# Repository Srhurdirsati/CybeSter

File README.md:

# CyberSter

Cyberster is a portable MP3 player using different electronic modules. It can play music from an SD card and send audio through AUX or Bluetooth. A screen is used to show the menu and song information. The device also uses a Type-C port for power and transferring music files.

## Complete Hardware & BOM Table

Go to bom.csv for BOM 

## Features 

> MP3 playback from SD card

> Scrollable music list

> Basic UI on TFT screen

> Play / Pause / Next / Previous controls

> Volume adjustment

> Sleep mode

> Automatic next-track playback

> Aux Output

The display needs to be just vertically mounted on the mounting poles .

## Usage 

> Install Arduino IDE.

> Install the ESP32 board package.

> Install the required libraries:

> Adafruit VS1053

> Adafruit GFX

> Adafruit ST7789

> SPI

> SD

> Open the firmware file.

> Select your ESP32 board.

> Upload the code.

Now you are done setting it up the firmware . 

Next you will need to plug the battery to the jst connector below the board and make sure its properly connected at appropriate poles. The buttons would be pressed by the 3d model of button which would be inserted from below the top plate at it's desired holes and it will automatically fit in that . No need to solder anything .

## Future Possible Updates

> Bt support

> Inbuilt Speaker

> Playlist

> Better Animations, etc.

## Images

## JLCPCB

This was my most difficult and complex project till now and most timetaking so I just wan't to say that PCB won't feel easy at all if you are a beginner and also make sure u have enough knowledge to start .

TFT = 13 USD, ESP-32 = 7 USD, JLC = 67 

Total = 87 USD With Shipping

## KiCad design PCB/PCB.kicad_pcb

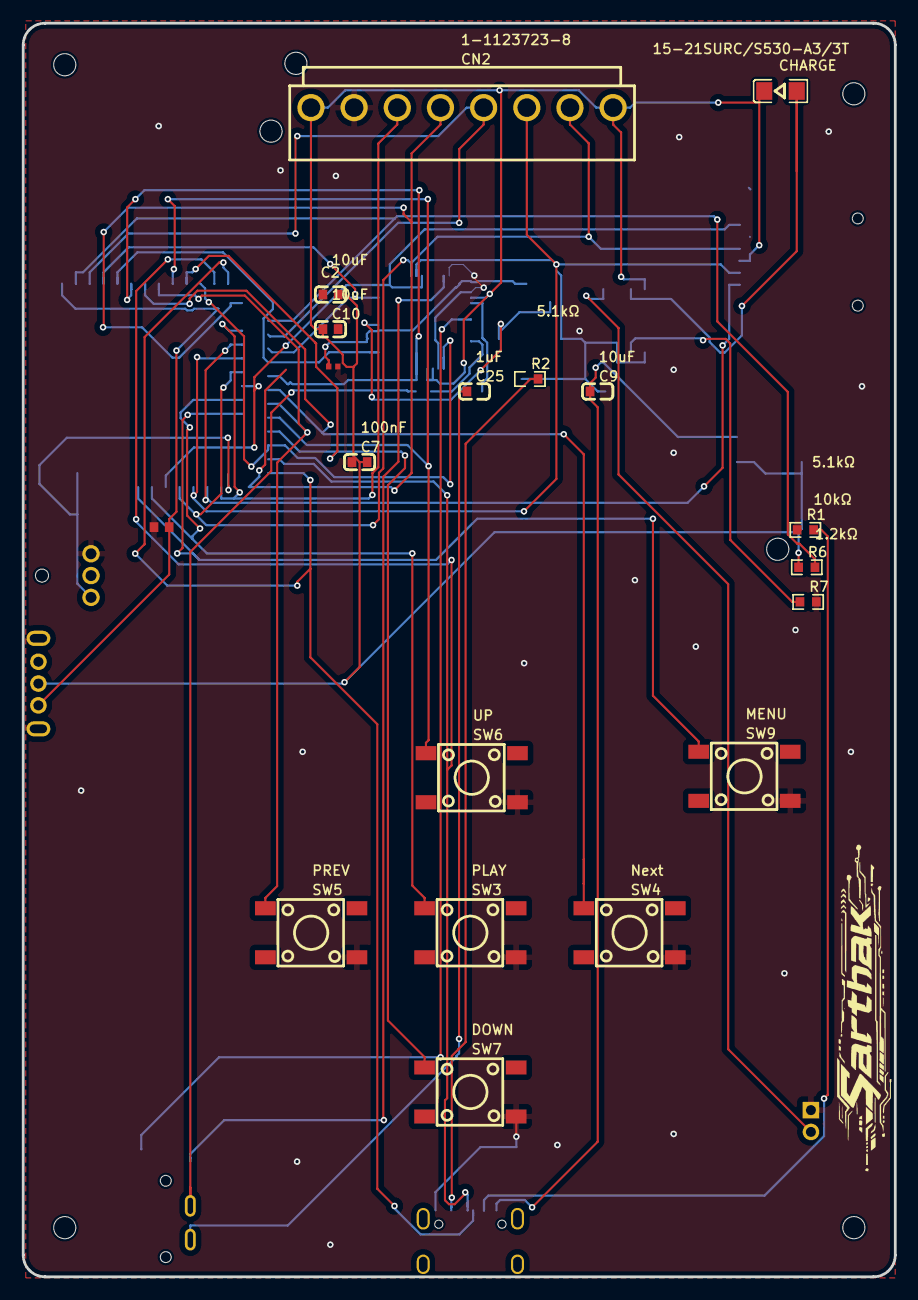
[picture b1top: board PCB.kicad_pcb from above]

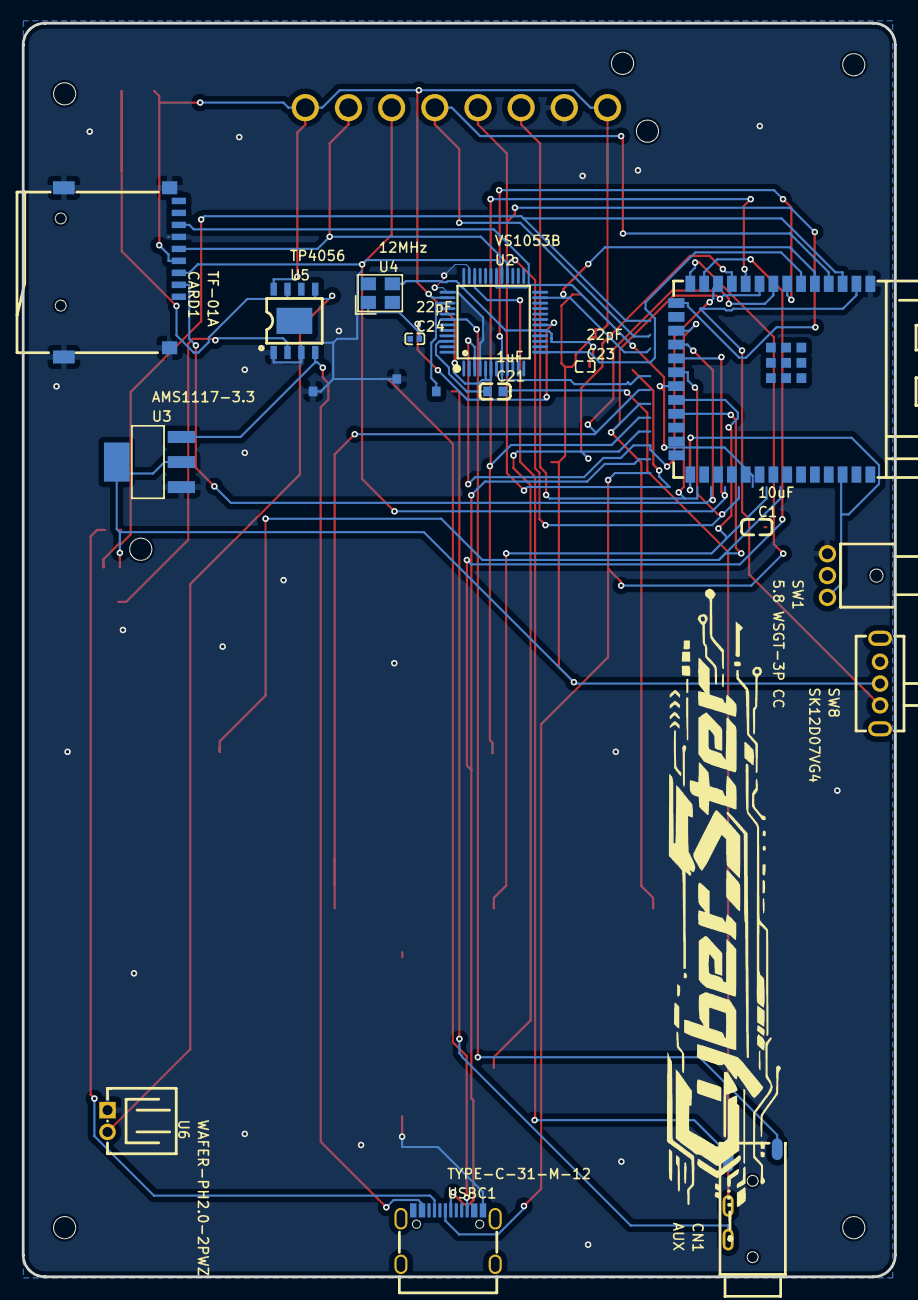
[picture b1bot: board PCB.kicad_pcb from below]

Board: 2 copper layers, 80.0 x 115.0 mm, 39 parts (15 on the bottom side), 38 nets.

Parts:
C1, C2, C9, C10: 10uF; C0603
C7: 100nF; C0603
C21, C25: 1uF; C0603
C23, C24: 22pF; C0402
CARD1: TF-01A; TF-SMD_TF-01A
CHARGE: 15-21SURC/S530-A3/3T; LED1206-R-RD_RED
CN1: AUX; AUDIO-SMD_HC-PJ-320A
CN2: 1-1123723-8; CONN-TH_1-1123723-8
Hole_gge20538: Hole_gge20538
Hole_gge20553: Hole_gge20553
Hole_gge20568: Hole_gge20568
Hole_gge20583: Hole_gge20583
Hole_gge20613: Hole_gge20613
Hole_gge20670: Hole_gge20670
Hole_gge20700: Hole_gge20700
R1, R2: 5.1kΩ; R0603
R6: 10kΩ; R0603
R7: 1.2kΩ; R0603
SW1: 5.8 WSGT-3P CC; SW-TH_3P-L5.8_WSGT-3P-CC
SW3: PLAY; KEY-SMD_4P-L6.0-W6.0-P4.50-LS9.0
SW4: Next; KEY-SMD_4P-L6.0-W6.0-P4.50-LS9.0
SW5: PREV; KEY-SMD_4P-L6.0-W6.0-P4.50-LS9.0
SW6: UP; KEY-SMD_4P-L6.0-W6.0-P4.50-LS9.0
SW7: DOWN; KEY-SMD_4P-L6.0-W6.0-P4.50-LS9.0
SW8: SK12D07VG4; SW-TH_SK12D07VG4
SW9: MENU; KEY-SMD_4P-L6.0-W6.0-P4.50-LS9.0
U1: ESP32; WIRELM-SMD_ESP32-S3-WROOM-1
U2: VS1053B; LQFP-48_L7.0-W7.0-P0.50-LS9.0-BL
U3: AMS1117-3.3; SOT-223-3_L6.5-W3.4-P2.30-LS7.0-BR
U4: 12MHz; CRYSTAL-SMD_4P-L3.2-W2.5-BL
U5: TP4056; ESOP-8_L4.9-W3.9-P1.27-LS6.0-BL-EP
U6: WAFER-PH2.0-2PWZ; CONN-TH_2P-P2.00_GP01-2001WR-2P
USBC1: TYPE-C-31-M-12; USB-C_SMD-TYPE-C-31-M-12_1

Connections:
3V: C2.2, C7.2, C10.1, CARD1.4, CHARGE.2, CN2.1, CN2.8, R6.1, SW8.2, U2.5, U2.6, U2.38, U3.2, U3.4, U5.8
5V: C9.1, U3.3, U5.4, USBC1.A4B9
DETECT: CN1.4, U2.34
GBUF: CN1.1, U2.42
GND: C1.2, C2.1, C7.1, C9.2, C10.2, C23.1, C24.1, CARD1.6, CARD1.10, CARD1.11, CARD1.12, CARD1.13, CN2.2, R1.1, R2.1, R7.2, SW1.3, SW3.4, SW4.4, SW5.4, SW6.4, SW7.4, SW9.4, U1.1, U2.4, U2.35, U2.37, U3.1, U5.1, U5.3, U6.1, USBC1.B1A12
LEFT: C21.2, CN1.3
MENU: SW9.1, U1.23
MISO: CARD1.7, U1.21, U2.30
MOSI: CARD1.3, CN2.6, U1.19, U2.29
NEXT: SW4.1, U1.8
PLAY: SW3.1, U1.22
PREV: SW5.1, U1.9
RIGHT: C25.1, CN1.2
SCLK: CARD1.5, CN2.7, U1.20, U2.28
SDCARDCS: CARD1.2, U1.18
SW3.3: C1.1, SW8.1, U1.2
TFTAO: CN2.5, U1.4
TFTT_RST: CN2.4, U1.15
TFT_CS: CN2.3, U1.17
U1_3: R6.2, U1.3
U1_27: SW1.1, U1.27
U2_39: C25.2, U2.39
U2_46: C21.1, U2.46
U5_2: R7.1, U5.2
U5_5: U5.5, U6.2
U5_7: CHARGE.1, U5.7
USBC1_A5: R1.2, USBC1.A5
USBC1_B5: R2.2, USBC1.B5
USBD+: U1.14, USBC1.A6
USBD-: U1.13, USBC1.A7
V+: SW6.1, U1.10
V-: SW7.1, U1.11
VS1053_DREQ: U1.7, U2.8
VS1053_RST: U1.12, U2.3
VS1053_XCS: U1.5, U2.23
VS1053_XDCS: U1.6, U2.13
XTALI: C24.2, U2.18, U4.1
XTALO: C23.2, U2.17, U4.3

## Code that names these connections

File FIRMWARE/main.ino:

#include <SPI.h>
#include <SD.h>
#include <Adafruit_VS1053.h>
#include <Adafruit_GFX.h>
#include <Adafruit_ST7789.h>

// VS1053
#define VS1053_CS 5
#define VS1053_DCS 6
#define VS1053_DREQ 7
#define VS1053_RST 8

// SD
#define SD_CS 10

// TFT
#define TFT_CS 9
#define TFT_DC 4
#define TFT_RST 3

// Buttons
#define BTN_PLAY 14
#define BTN_NEXT 15
#define BTN_PREV 16
#define BTN_UP 17
#define BTN_DOWN 18
#define BTN_MENU 21

// Battery
#define BAT_ADC 1

#define MAX_SONGS 200
#define SCREEN_W 240
#define SCREEN_H 240

Adafruit_ST7789 tft = Adafruit_ST7789(TFT_CS, TFT_DC, TFT_RST);

Adafruit_VS1053_FilePlayer player =
Adafruit_VS1053_FilePlayer(
VS1053_RST,
VS1053_CS,
VS1053_DCS,
VS1053_DREQ,
SD_CS
);

String songList[MAX_SONGS];
int songCount = 0;

int selected = 0;
int currentSong = -1;

bool playing = false;

int volume = 20;

int scrollOffset = 0;

unsigned long lastUI = 0;

void scanFiles(File dir) {

while(true){

File entry = dir.openNextFile();

if(!entry) break;

String name = entry.name();

if(name.endsWith(".MP3") || name.endsWith(".mp3")){

songList[songCount++] = name;

}

entry.close();

}

}

float readBattery(){

int raw = analogRead(BAT_ADC);

float voltage = raw * (3.3 / 4095.0) * 2;

return voltage;

}

int batteryPercent(){

float v = readBattery();

if(v >= 4.2) return 100;
if(v >= 4.0) return 85;
if(v >= 3.8) return 60;
if(v >= 3.6) return 40;
if(v >= 3.4) return 20;
return 5;

}

void drawHeader(){

tft.fillRect(0,0,240,30,ST77XX_BLUE);

tft.setCursor(5,8);
tft.setTextColor(ST77XX_WHITE);
tft.setTextSize(2);
tft.print("MP3 Player");

int bat = batteryPercent();

tft.setCursor(180,8);
tft.print(bat);
tft.print("%");

}

void drawList(){

tft.fillRect(0,30,240,170,ST77XX_BLACK);

for(int i=0;i<6;i++){

int index = scrollOffset + i;

if(index >= songCount) break;

if(index == selected){

tft.fillRect(0,30 + i*28,240,28,ST77XX_GREEN);

tft.setTextColor(ST77XX_BLACK);

}else{

tft.setTextColor(ST77XX_WHITE);

}

tft.setCursor(10,40 + i*28);

tft.print(songList[index]);

}

}

void drawPlayer(){

tft.fillRect(0,30,240,170,ST77XX_BLACK);

tft.setCursor(10,40);
tft.print("Playing:");

tft.setCursor(10,70);
tft.print(songList[currentSong]);

}

void drawProgress(){

if(!player.playingMusic) return;

uint32_t pos = player.currentPosition();
uint32_t len = player.playingMusicSize;

if(len == 0) return;

int w = (pos * 200) / len;

tft.drawRect(20,200,200,10,ST77XX_WHITE);

tft.fillRect(20,200,w,10,ST77XX_GREEN);

}

void playSelected(){

currentSong = selected;

player.stopPlaying();

player.startPlayingFile(songList[currentSong].c_str());

playing = true;

drawPlayer();

}

void handleButtons(){

if(!digitalRead(BTN_UP)){

selected--;

if(selected < 0) selected = 0;

if(selected < scrollOffset) scrollOffset--;

drawList();

delay(150);

}

if(!digitalRead(BTN_DOWN)){

selected++;

if(selected >= songCount) selected = songCount -1;

if(selected > scrollOffset + 5) scrollOffset++;

drawList();

delay(150);

}

if(!digitalRead(BTN_PLAY)){

if(currentSong == selected){

if(playing){

player.pausePlaying(true);

playing=false;

}else{

player.pausePlaying(false);

playing=true;

}

}else{

playSelected();

}

delay(200);

}

if(!digitalRead(BTN_NEXT)){

selected++;

if(selected >= songCount) selected = 0;

playSelected();

delay(200);

}

if(!digitalRead(BTN_PREV)){

selected--;

if(selected < 0) selected = songCount-1;

playSelected();

delay(200);

}

}

void sleepMode(){

player.stopPlaying();

tft.fillScreen(ST77XX_BLACK);

tft.setCursor(60,120);
tft.print("Sleeping");

delay(2000);

esp_deep_sleep_start();

}

void setup(){

Serial.begin(115200);

pinMode(BTN_PLAY,INPUT_PULLUP);
pinMode(BTN_NEXT,INPUT_PULLUP);
pinMode(BTN_PREV,INPUT_PULLUP);
pinMode(BTN_UP,INPUT_PULLUP);
pinMode(BTN_DOWN,INPUT_PULLUP);
pinMode(BTN_MENU,INPUT_PULLUP);

tft.init(240,240);
tft.setRotation(2);

if(!SD.begin(SD_CS)){

tft.print("SD Error");

while(1);

}

if(!player.begin()){

tft.print("VS1053 Error");

while(1);

}

player.setVolume(volume,volume);

scanFiles(SD.open("/"));

drawHeader();
drawList();

}

void loop(){

handleButtons();

if(millis() - lastUI > 300){

drawProgress();

drawHeader();

lastUI = millis();

}

if(!player.playingMusic && playing){

selected++;

if(selected >= songCount) selected = 0;

playSelected();

}

if(!digitalRead(BTN_MENU)){

sleepMode();

}

}

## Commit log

2026-03-16 Create FABRICATION
2026-03-16 Update README with display connection details and costs
    Added information about display connection and cost breakdown.
2026-03-18 Fix typo in README animations section
